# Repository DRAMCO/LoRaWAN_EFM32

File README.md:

# LoRaWAN_EFM32

LoRaMAC implementation based on the Semtech implemenation for the EFM32 Happy Gecko develop board.
Developed by [DRAMCO](http://www.dramco.be).

This project will be used in hands-on sessions to let attendees experience the development of low power IoT nodes.
The module was used in the following tutorials:
- [IEEE Sensors 2017](http://ieee-sensors2017.org/low-power-wireless-technologies-connecting-embedded-sensors-iot-journey-fundaments-hands)
- [IEEE PIMRC 2017](http://pimrc2017.ieee-pimrc.org/program/tutorials-2/)
- Workshop: [Connecting Embedded Sensors in the IoT](https://dramco.be/tutorials/connecting-embedded-sensors-in-the-iot)

The hands-on can be found [here](dramco.be/tutorials/low-power-iot) with the corresponding [presentation](https://www.slideshare.net/GillesCallebaut/low-power-wireless-technologies-for-connecting-embedded-sensors-in-the-iot-a-journey-from-fundaments-to-handson-90398582).

The DRAMCO LoRa module features a Semtech SX1272 Radio chip and an EFM32 Cortex M0 processor. 

## How to cite
```LaTex
@Misc{lorawan-efm32,
  author =   {G. Ottoy and G. Leenders and G. Callebaut},
  title =    {{LoRaWAN EFM32}},
  url = {https://github.com/DRAMCO/LoRaWAN_EFM32},
  note = {doi: \url{10.5281/zenodo.1209414}}
}
```

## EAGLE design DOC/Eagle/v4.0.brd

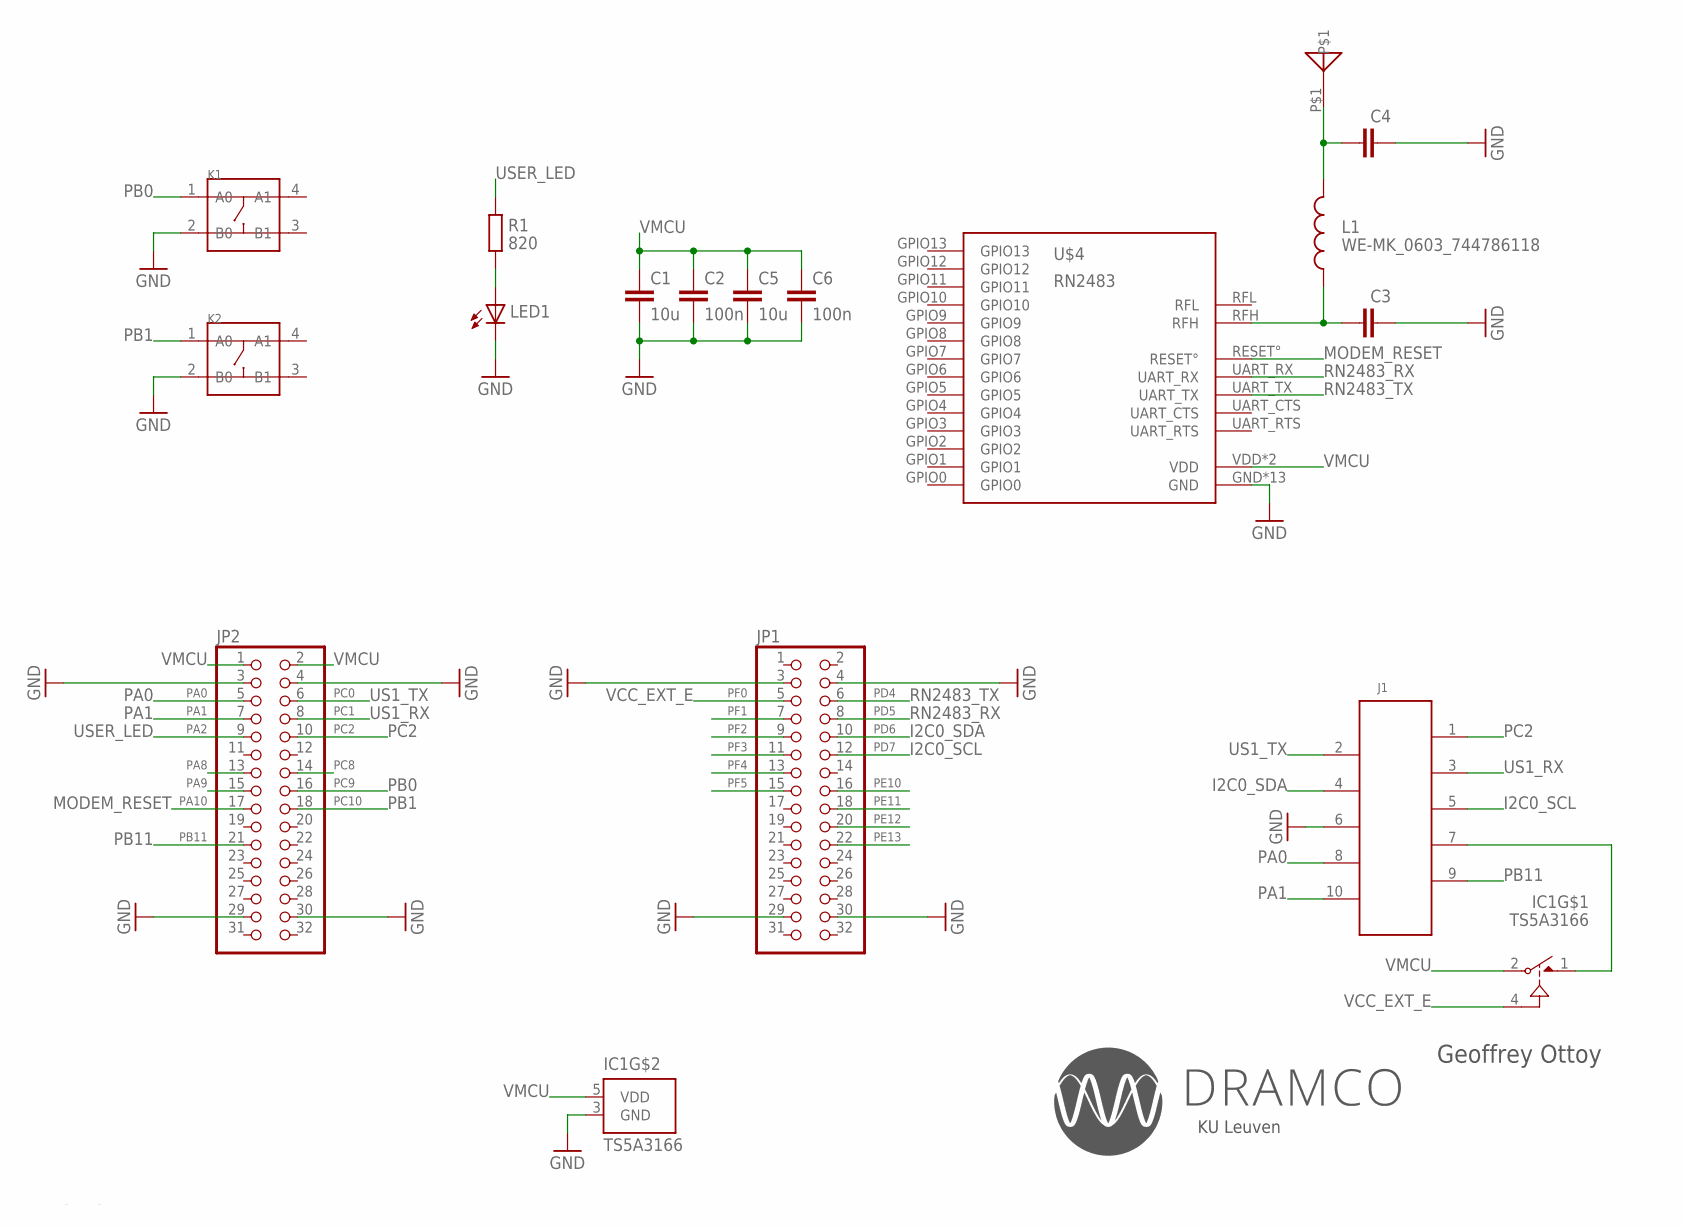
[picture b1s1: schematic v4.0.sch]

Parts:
C1, C5: 10u; C0805K
C2, C6: 100n; C0805K
C3, C4: C-EUC0603K; C0603K
IC1: TS5A3166; SC70-5L
J1: 61001018321
JP1, JP2: PINHD-2X16; 2X16
K1, K2: SMD-SWITCH-TACTILE-SPST-NO(4P-D6.0MM); SW4-SMD-6.0X6.0X5.0MM
L1: WE-MK_0603_744786118; WE-MK_0603
LED1: LEDCHIPLED_0805; CHIPLED_0805
R1: 820; R0805
U$2: ANTENNA868; CERAMIC-ANTENNA
U$4: RN2483

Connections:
GND: C1.2, C2.2, C3.1, C4.1, C5.2, C6.2, IC1.3 (GND), J1.6 (5), JP1.3, JP1.4, JP1.29, JP1.30, JP2.3, JP2.4, JP2.29, JP2.30, K1.2 (B0), K2.2 (B0), LED1.C, U$4.GND, U$4.GND1 (GND), U$4.GND2 (GND), U$4.GND3 (GND), U$4.GND4 (GND), U$4.GND5 (GND), U$4.GND6 (GND), U$4.GND7 (GND), U$4.GND8 (GND), U$4.GND9 (GND), U$4.GND10 (GND), U$4.GND11 (GND), U$4.GND12 (GND)
unnamed: LED1.A, R1.1
unnamed: C3.2, L1.1, U$4.RFH
unnamed: C4.2, L1.2, U$2.P$1
unnamed: IC1.1 (NO), J1.7 (4)
PA0: J1.8 (3), JP2.5
PA1: J1.10 (1), JP2.7
PA2: JP2.9, R1.2
PA8: JP2.13
PA9: JP2.15
PA10: JP2.17, U$4.RESET°
PB11: J1.9 (2), JP2.21
PC0: J1.2 (9), JP2.6
PC1: J1.3 (8), JP2.8
PC2: J1.1 (10), JP2.10
PC8: JP2.14
PC9: JP2.16, K1.1 (A0)
PC10: JP2.18, K2.1 (A0)
PD4: JP1.6, U$4.UART_TX
PD5: JP1.8, U$4.UART_RX
PD6: J1.4 (7), JP1.10
PD7: J1.5 (6), JP1.12
PE10: JP1.16
PE11: JP1.18
PE12: JP1.20
PE13: JP1.22
PF0: IC1.4 (IN), JP1.5
PF1: JP1.7
PF2: JP1.9
PF3: JP1.11
PF4: JP1.13
PF5: JP1.15
VMCU: C1.1, C2.1, C5.1, C6.1, IC1.2 (COM), IC1.5 (VDD), JP2.1, JP2.2, U$4.VDD, U$4.VDD2 (VDD)

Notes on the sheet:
Geoffrey Ottoy
KU Leuven
I2C0_SDA
I2C0_SCL
PC2
PB0
PB1
PA0
PA1
PB11
MODEM_RESET
RN2483_RX
RN2483_TX
US1_TX
US1_RX
USER_LED
VCC_EXT_E

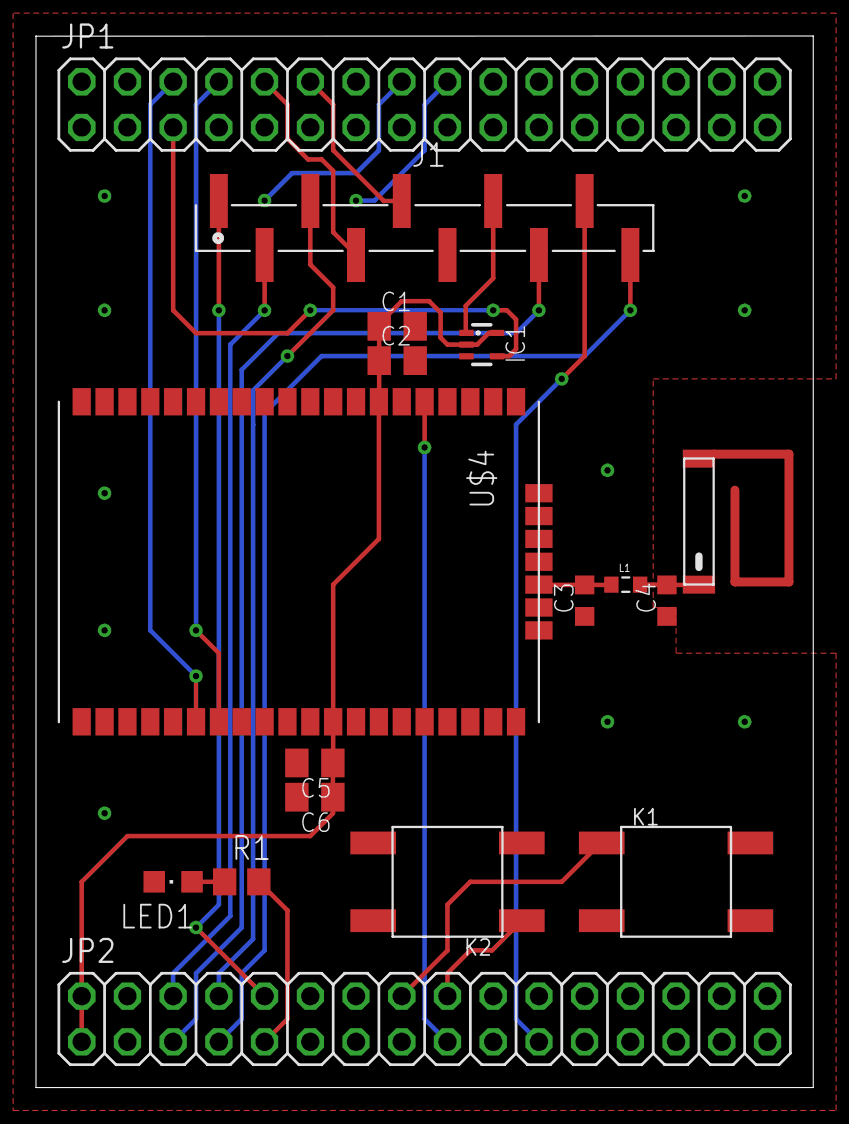
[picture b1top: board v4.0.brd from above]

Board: 2 copper layers, 43.2 x 58.4 mm, 17 parts (0 on the bottom side), 21 nets.

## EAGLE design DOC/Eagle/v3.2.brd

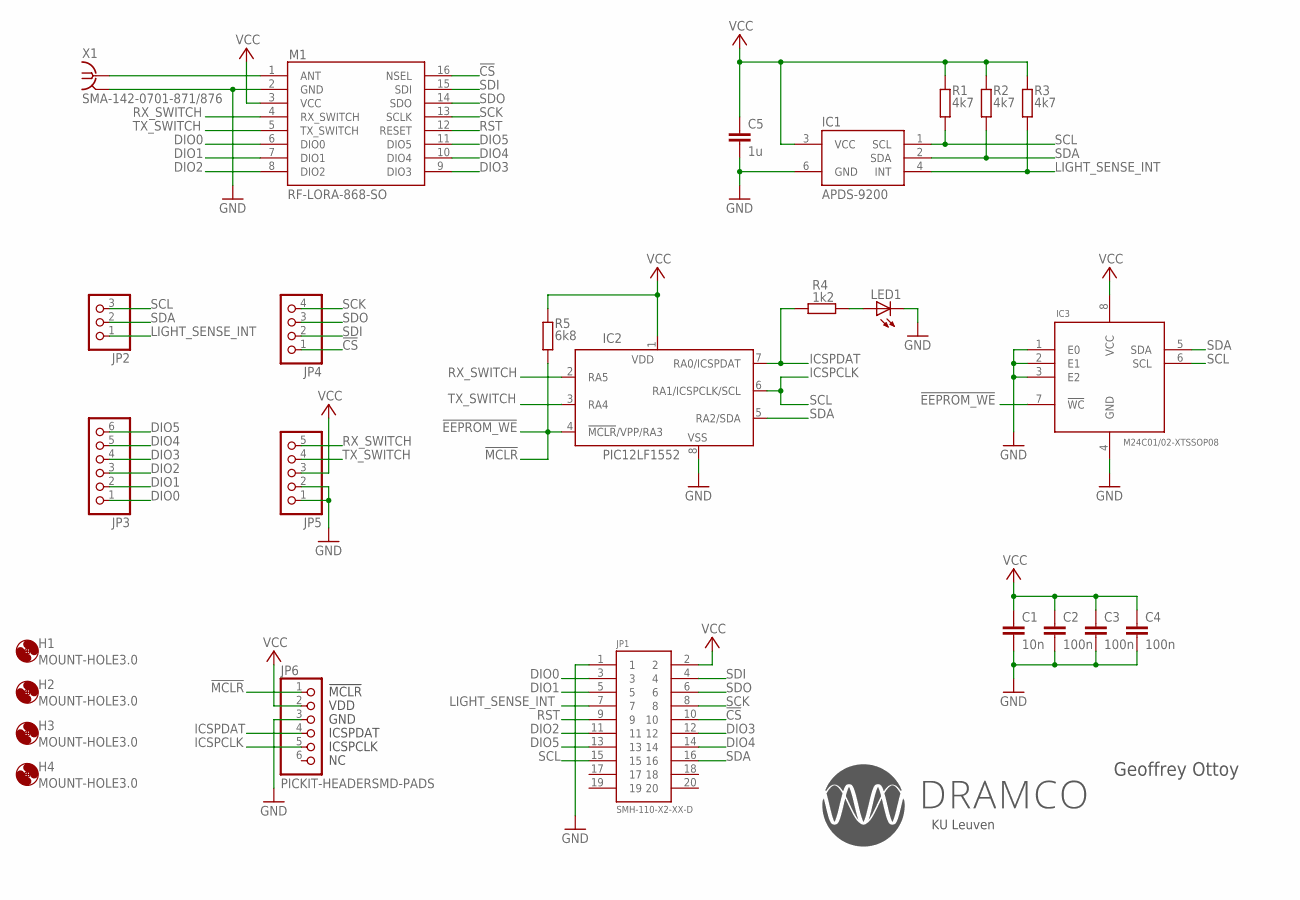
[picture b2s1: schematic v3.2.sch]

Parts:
C1: 10n; C0805K
C2, C3, C4: 100n; C0805K
C5: 1u; C0805K
H1, H2, H3, H4: MOUNT-HOLE3.0; 3,0
IC1: APDS-9200
IC2: PIC12LF1552; MSOP8
IC3: M24C01/02-XTSSOP08; TSSOP08
JP1: SMH-110-X2-XX-D
JP2: PINHD-1X3; 1X03
JP3: PINHD-1X6; 1X06
JP4: PINHD-1X4; 1X04
JP5: PINHD-1X5; 1X05
JP6: PICKIT-HEADERSMD-PADS; 1X06/SMD
LED1: LEDCHIP-LED0805; CHIP-LED0805
M1: RF-LORA-868-SO
R1, R2, R3: 4k7; M0805
R4: 1k2; M0805
R5: 6k8; M0805
X1: SMA-142-0701-871/876; J502-ND-142-0701-871/876

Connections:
!CS: JP1.10, JP4.1, M1.16 (NSEL)
!MCLR: IC2.4 (!MCLR!/VPP/RA3), IC3.7 (!WC), JP6.1, R5.1
ANT: M1.1 (ANT), X1.1
DIO0: JP1.3, JP3.1, M1.6 (DIO0)
DIO1: JP1.5, JP3.2, M1.7 (DIO1)
DIO2: JP1.11, JP3.3, M1.8 (DIO2)
DIO3: JP1.12, JP3.4, M1.9 (DIO3)
DIO4: JP1.14, JP3.5, M1.10 (DIO4)
DIO5: JP1.13, JP3.6, M1.11 (DIO5)
GND: C1.2, C2.2, C3.2, C4.2, C5.2, IC1.6 (GND), IC2.8 (VSS), IC3.1 (E0), IC3.2 (E1), IC3.3 (E2), IC3.4 (GND), JP1.1, JP5.1, JP5.2, JP6.3, LED1.C, M1.2 (GND), X1.G@1 (2), X1.G@2 (2), X1.G@3 (2), X1.G@4 (2)
ICSPDAT: IC2.7 (RA0/ICSPDAT), JP6.4, R4.2
LIGHT_SENSE_INT: IC1.4 (INT), JP1.7, JP2.1, R3.1
unnamed: LED1.A, R4.1
RST: JP1.9, M1.12 (RESET)
RX_SWITCH: IC2.2 (RA5), JP5.5, M1.4 (RX_SWITCH)
SCK: JP1.8, JP4.4, M1.13 (SCLK)
SCL: IC1.1 (SCL), IC2.6 (RA1/ICSPCLK/SCL), IC3.6 (SCL), JP1.15, JP2.3, JP6.5, R1.1
SDA: IC1.2 (SDA), IC2.5 (RA2/SDA), IC3.5 (SDA), JP1.16, JP2.2, R2.1
SDI: JP1.4, JP4.2, M1.15 (SDI)
SDO: JP1.6, JP4.3, M1.14 (SDO)
TX_SWITCH: IC2.3 (RA4), JP5.4, M1.5 (TX_SWITCH)
VCC: C1.1, C2.1, C3.1, C4.1, C5.1, IC1.3 (VCC), IC2.1 (VDD), IC3.8 (VCC), JP1.2, JP5.3, JP6.2, M1.3 (VCC), R1.2, R2.2, R3.2, R5.2

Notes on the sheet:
Geoffrey Ottoy
KU Leuven
ICSPCLK
!EEPROM_WE

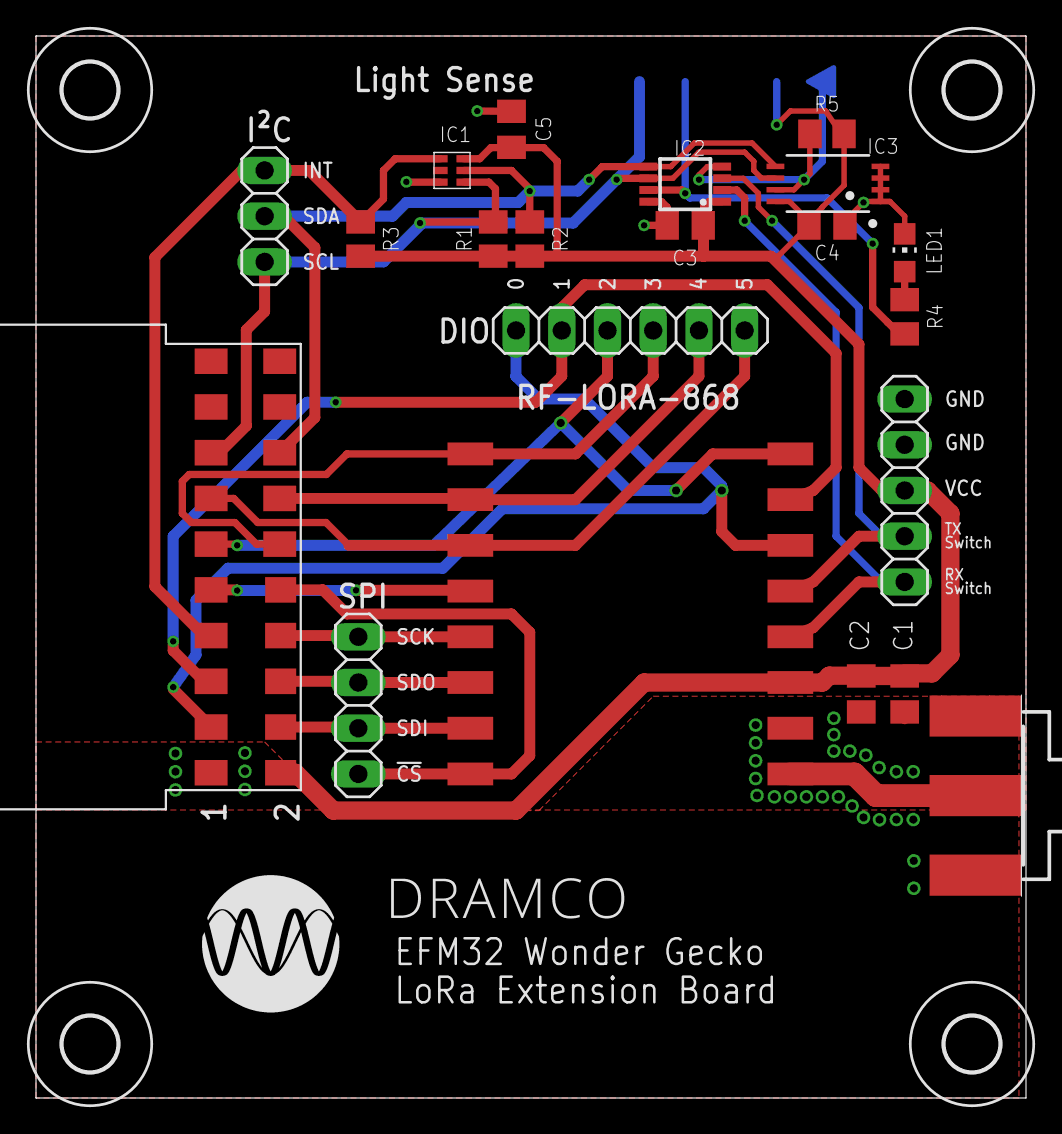
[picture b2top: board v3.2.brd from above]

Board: 2 copper layers, 55.0 x 59.0 mm, 26 parts (1 on the bottom side), 22 nets.

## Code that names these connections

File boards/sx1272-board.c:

/*
 / _____)             _              | |
( (____  _____ ____ _| |_ _____  ____| |__
 \____ \| ___ |    (_   _) ___ |/ ___)  _ \
 _____) ) ____| | | || |_| ____( (___| | | |
(______/|_____)_|_|_| \__)_____)\____)_| |_|
    (C)2013 Semtech

Description: SX1272 driver specific target board functions implementation

License: Revised BSD License, see LICENSE.TXT file include in the project

Maintainer: Miguel Luis and Gregory Cristian
*/
#include "board.h"
#include "radio.h"
#include "sx1272.h"
#include "sx1272-board.h"
#ifdef HW_VERSION_3
#include "omux-board.h"
#endif

/*!
 * Flag used to set the RF switch control pins in low power mode when the radio is not active.
 */
static bool RadioIsActive = false;

/*!
 * Radio driver structure initialization
 */
const struct Radio_s Radio =
{
    SX1272Init,
    SX1272GetStatus,
    SX1272SetModem,
    SX1272SetChannel,
    SX1272IsChannelFree,
    SX1272Random,
    SX1272SetRxConfig,
    SX1272SetTxConfig,
    SX1272CheckRfFrequency,
    SX1272GetTimeOnAir,
    SX1272Send,
    SX1272SetSleep,
    SX1272SetStby,
    SX1272SetRx,
    SX1272StartCad,
    SX1272SetTxContinuousWave,
    SX1272ReadRssi,
    SX1272Write,
    SX1272Read,
    SX1272WriteBuffer,
    SX1272ReadBuffer,
    SX1272SetMaxPayloadLength,
    SX1272SetPublicNetwork
};

/*!
 * Antenna switch GPIO pins objects
 */
Gpio_t AntRx;
Gpio_t AntTx;

void SX1272IoInit( void )
{
    GpioInit( &SX1272.Spi.Nss, RADIO_NSS, PIN_OUTPUT, PIN_PUSH_PULL, PIN_PULL_UP, 1 );

    GpioInit( &SX1272.DIO0, RADIO_DIO_0, PIN_INPUT, PIN_PUSH_PULL, PIN_PULL_UP, 0 );
    GpioInit( &SX1272.DIO1, RADIO_DIO_1, PIN_INPUT, PIN_PUSH_PULL, PIN_PULL_UP, 0 );
    GpioInit( &SX1272.DIO2, RADIO_DIO_2, PIN_INPUT, PIN_PUSH_PULL, PIN_PULL_UP, 0 );
    GpioInit( &SX1272.DIO3, RADIO_DIO_3, PIN_INPUT, PIN_PUSH_PULL, PIN_PULL_UP, 0 );
    GpioInit( &SX1272.DIO4, RADIO_DIO_4, PIN_INPUT, PIN_PUSH_PULL, PIN_PULL_UP, 0 );
    GpioInit( &SX1272.DIO5, RADIO_DIO_5, PIN_INPUT, PIN_PUSH_PULL, PIN_PULL_UP, 0 );
}

void SX1272IoIrqInit( DioIrqHandler **irqHandlers )
{
    GpioSetInterrupt( &SX1272.DIO0, IRQ_RISING_EDGE, IRQ_HIGH_PRIORITY, irqHandlers[0] );
    GpioSetInterrupt( &SX1272.DIO1, IRQ_RISING_EDGE, IRQ_HIGH_PRIORITY, irqHandlers[1] );
    GpioSetInterrupt( &SX1272.DIO2, IRQ_RISING_EDGE, IRQ_HIGH_PRIORITY, irqHandlers[2] );
    GpioSetInterrupt( &SX1272.DIO3, IRQ_RISING_EDGE, IRQ_HIGH_PRIORITY, irqHandlers[3] );
    GpioSetInterrupt( &SX1272.DIO4, IRQ_RISING_EDGE, IRQ_HIGH_PRIORITY, irqHandlers[4] );
    //GpioSetInterrupt( &SX1272.DIO5, IRQ_RISING_EDGE, IRQ_HIGH_PRIORITY, irqHandlers[5] );
}

void SX1272IoDeInit( void )
{
    GpioInit( &SX1272.Spi.Nss, RADIO_NSS, PIN_OUTPUT, PIN_PUSH_PULL, PIN_PULL_UP, 1 );

    GpioInit( &SX1272.DIO0, RADIO_DIO_0, PIN_INPUT, PIN_PUSH_PULL, PIN_NO_PULL, 0 );
    GpioInit( &SX1272.DIO1, RADIO_DIO_1, PIN_INPUT, PIN_PUSH_PULL, PIN_NO_PULL, 0 );
    GpioInit( &SX1272.DIO2, RADIO_DIO_2, PIN_INPUT, PIN_PUSH_PULL, PIN_NO_PULL, 0 );
    GpioInit( &SX1272.DIO3, RADIO_DIO_3, PIN_INPUT, PIN_PUSH_PULL, PIN_NO_PULL, 0 );
    GpioInit( &SX1272.DIO4, RADIO_DIO_4, PIN_INPUT, PIN_PUSH_PULL, PIN_NO_PULL, 0 );
    GpioInit( &SX1272.DIO5, RADIO_DIO_5, PIN_INPUT, PIN_PUSH_PULL, PIN_NO_PULL, 0 );
}

void SX1272SetRfTxPower( int8_t power )
{
    uint8_t paConfig = 0;
    uint8_t paDac = 0;

    paConfig = SX1272Read( REG_PACONFIG );
    paDac = SX1272Read( REG_PADAC );

    paConfig = ( paConfig & RF_PACONFIG_PASELECT_MASK ) | SX1272GetPaSelect( SX1272.Settings.Channel );

    if( ( paConfig & RF_PACONFIG_PASELECT_PABOOST ) == RF_PACONFIG_PASELECT_PABOOST )
    {
        if( power > 17 )
        {
            paDac = ( paDac & RF_PADAC_20DBM_MASK ) | RF_PADAC_20DBM_ON;
        }
        else
        {
            paDac = ( paDac & RF_PADAC_20DBM_MASK ) | RF_PADAC_20DBM_OFF;
        }
        if( ( paDac & RF_PADAC_20DBM_ON ) == RF_PADAC_20DBM_ON )
        {
            if( power < 5 )
            {
                power = 5;
            }
            if( power > 20 )
            {
                power = 20;
            }
            paConfig = ( paConfig & RFLR_PACONFIG_OUTPUTPOWER_MASK ) | ( uint8_t )( ( uint16_t )( power - 5 ) & 0x0F );
        }
        else
        {
            if( power < 2 )
            {
                power = 2;
            }
            if( power > 17 )
            {
                power = 17;
            }
            paConfig = ( paConfig & RFLR_PACONFIG_OUTPUTPOWER_MASK ) | ( uint8_t )( ( uint16_t )( power - 2 ) & 0x0F );
        }
    }
    else
    {
        if( power < -1 )
        {
            power = -1;
        }
        if( power > 14 )
        {
            power = 14;
        }
        paConfig = ( paConfig & RFLR_PACONFIG_OUTPUTPOWER_MASK ) | ( uint8_t )( ( uint16_t )( power + 1 ) & 0x0F );
    }
    SX1272Write( REG_PACONFIG, paConfig );
    SX1272Write( REG_PADAC, paDac );
}

uint8_t SX1272GetPaSelect( uint32_t channel )
{
    return RF_PACONFIG_PASELECT_PABOOST;
}

void SX1272SetAntSwLowPower( bool status )
{
    if( RadioIsActive != status )
    {
        RadioIsActive = status;

        if( status == false )
        {
            SX1272AntSwInit( );
        }
        else
        {
            SX1272AntSwDeInit( );
        }
    }
}

void SX1272AntSwInit( void )
{
#ifndef HW_VERSION_3
    GpioInit( &AntTx, RADIO_ANT_SWITCH_TX, PIN_OUTPUT, PIN_PUSH_PULL, PIN_PULL_UP, 0 );
    GpioInit( &AntRx, RADIO_ANT_SWITCH_RX, PIN_OUTPUT, PIN_PUSH_PULL, PIN_PULL_UP, 1 );
#else
    OMuxAntInit();
#endif
}

void SX1272AntSwDeInit( void )
{
#ifndef HW_VERSION_3
    GpioInit( &AntTx, RADIO_ANT_SWITCH_TX, PIN_ANALOGIC, PIN_PUSH_PULL, PIN_NO_PULL, 0 );
    GpioInit( &AntRx, RADIO_ANT_SWITCH_RX, PIN_ANALOGIC, PIN_PUSH_PULL, PIN_NO_PULL, 0 );
#endif
}

void SX1272SetAntSw( uint8_t opMode )
{
    switch( opMode )
    {
    case RFLR_OPMODE_TRANSMITTER:
#ifndef HW_VERSION_3
        GpioWrite( &AntRx, 0 );
        GpioWrite( &AntTx, 1 );
#else
        OMuxAntSetTX();
#endif
        break;
    case RFLR_OPMODE_RECEIVER:
    case RFLR_OPMODE_RECEIVER_SINGLE:
    case RFLR_OPMODE_CAD:
    default:
#ifndef HW_VERSION_3
        GpioWrite( &AntRx, 1 );
        GpioWrite( &AntTx, 0 );
#else
        OMuxAntSetRX();
#endif
        break;
    }
}

bool SX1272CheckRfFrequency( uint32_t frequency )
{
    // Implement check. Currently all frequencies are supported
    return true;
}

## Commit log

2017-07-12 :circus_tent: Added .gitattributes & .gitignore files
2017-07-13 Added AES hardware support
    Define USE_AES_HW (preprocessor symbol) to enable AES hardware
    operations. Otherwise, the standard software implementation will be
    used.
2017-07-13 Fixed em_lib path problem
    File links to SDK path locations were omitted. Actual em_lib files are
    being used instead.
2017-07-13 Ignore compiled source directories (test)
2017-07-13 Deleted compiled source folder
2017-07-13 Deleted file
2017-07-13 Changes to .gitignore (test 2)
2017-07-13 Working version (no OTA)
2017-07-14 Remapped GPIO interrupts
    GPIO interrupt pins have been remapped based on our own hardware
    implementation.
2017-07-14 Added push button support
    Added support to use the push buttons. A button press genererates an
    interrupt.
2017-07-14 Added some GPIO stuff to the main app
    LED1 blinks on transmission (very short, but has an impact on the power
    consumption).
    A press on PB0 toggles LED0.
2017-07-14 Sleep now fallse back to EM2
2017-07-14 Pre-vacation alpha
    Changes:
    OTAA works (only without USE_AES_HW)
    Omitted the use of linked source files (startup_gcc_efm32hg.s &
    system_efm32hg.c)
    Removed DIO5 interrupt
2017-07-14 Hardware design of the wonder gecko breakout board
    Eagle files for the EFM32 (M0 Cortex) Wonder Gecko Breakout board
    developed by DraMCo.
    Version 1 has been made (and heavily bodged).
    Version 2 is under development.
2017-07-17 Updated hardware schematic
2017-07-18 Updated hardware design
    Finished schematic (final checks needed!)
    Included pdf of the schematic
    First version of the board (no silkscreen yet)
2017-07-18 Updated board design
2017-07-19 Create LICENSE
2017-07-19 Minor Readme.md changes
2017-07-19 Final touches to board design, Gerber files
2017-07-31 Updated TODO list
2017-07-31 Deleted unused files
    Unused files were deleted.
2017-08-23 Added datasheets for several components
2017-08-23 Added new "LoRa Extension Board" design
    Hopefully this design will fix the issues encountered with the previous one.
    Added EEPROM and an output pin mux on the I2C bus. Remapped lines to the extension header.
2017-08-23 Added component list for the extension board
2017-08-25 Updated component list
    1) Fixed wrong component name for APDS-9200
    2) Added possible suppliers to the partlist
2017-09-01 added more HW versions
2017-09-05 Update HW design of the extension board
    Rerouted RST, SDA and SCL
2017-09-05 I2C outputmux submodule
2017-09-19 Integration of I2C
    I2C working.
    I2C output mux (on expansion board) working.
2017-09-19 Added temp. and humid. sensor support
    Added code to read out the wonder gecko's on-board SI7021 sensor.
2017-09-19 First version of application switching
    The main function now calls a specific main for each tutorial-application.
2017-09-21 Added and modified applications
    * Changes made to app selecting (global definition).
    * USE_AES_HW global symbol now has value 1 or 0 (use HW or not).
    * aes_app example completed.
2017-09-21 Example application added
    Example app for data accumulation
2017-09-21 Added deep sleep app
    Wake up on button press. Send message to the world. Go back to sleep.
2017-09-25 Chnaged the app selection method
2017-09-27 Added extra comments to the example projects
2017-09-27 small changes
2017-09-27 typo
2017-09-28 added nul terminating to string
2017-09-28 AES hardware bug fix
    Fixed hard fault that occured when using misaligned memory buffers as input to encrypt_aes().
2017-09-28 Fixed small error in documentation
2017-09-28 documentation fix
2017-09-28 added documentation to the diff keys
2017-09-28 Made changes to the omux and si7021 API
2017-09-29 Added I2C EEPROM API
    Allows for reading from and writing to the EEPROM memory on the LoRa expansion board. v3.0 and v3.1 of the hardware need rewiring in order to work with the EEPROM.
2017-09-29 Minor changes
    * Small changes in EEPROM implementation.
    * Replaced "Wonder Gecko" with "Happy Gecko"
2017-10-03 Define payloadlength
    Testen door Gilles
2017-10-03 auto calculate payloadLength without \0
2017-10-03 added error so people change the payload before running the app
2017-10-04 Added selection 433/868/915 to pcb (v3.2)
2017-10-04 Updated power consumption measurements
2017-10-04 removed error from comments
2017-10-05 changed symbols for 915MHz
2017-10-25 do not use device address en network app session key if OTAA
2017-10-28 USE_BAND_868
    Because were in a civilized part of the world.
2017-10-29 Small fix
    OTAA/APB key conflict in aes_app.c
2018-03-01 New hardware design
    Added v4.0 hardware
    Removed older hardware versions
    v4.0 and v3.2 are the only two versions in use.
2018-03-22 use RTC_IntGetEnabled() instead of RTC_IntGet() & RTC->IEN
2018-03-28 Updated build settings
2018-03-28 added figure
2018-03-28 added doi
